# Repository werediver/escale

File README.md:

# Kitchen / coffee scale

This is a kitchen / coffee scale project repository. Contains both the hardware design files and the firmware source code.

## Prototype one

- [Raspberry Pi Pico](https://www.raspberrypi.com/products/raspberry-pi-pico/)
- Firmware in Rust ([escale_fw_rs](escale_fw_rs/))
- Battery powered (AA×2)

## Prototype zero

The firmware source code is at a very early stage of development. See [escale_fw](escale_fw).

The hardware prototype is assembled on a breadboard and consists of the following components:

- [Seeeduino XIAO](https://wiki.seeedstudio.com/Seeeduino-XIAO/)
- [0.96" SSD1315 OLED display](https://wiki.seeedstudio.com/Grove-OLED-Display-0.96-SSD1315/)
- [MikroE Load Cell 2 Click](https://www.mikroe.com/load-cell-2-click)
- Two 12 mm THT-mount push-buttons

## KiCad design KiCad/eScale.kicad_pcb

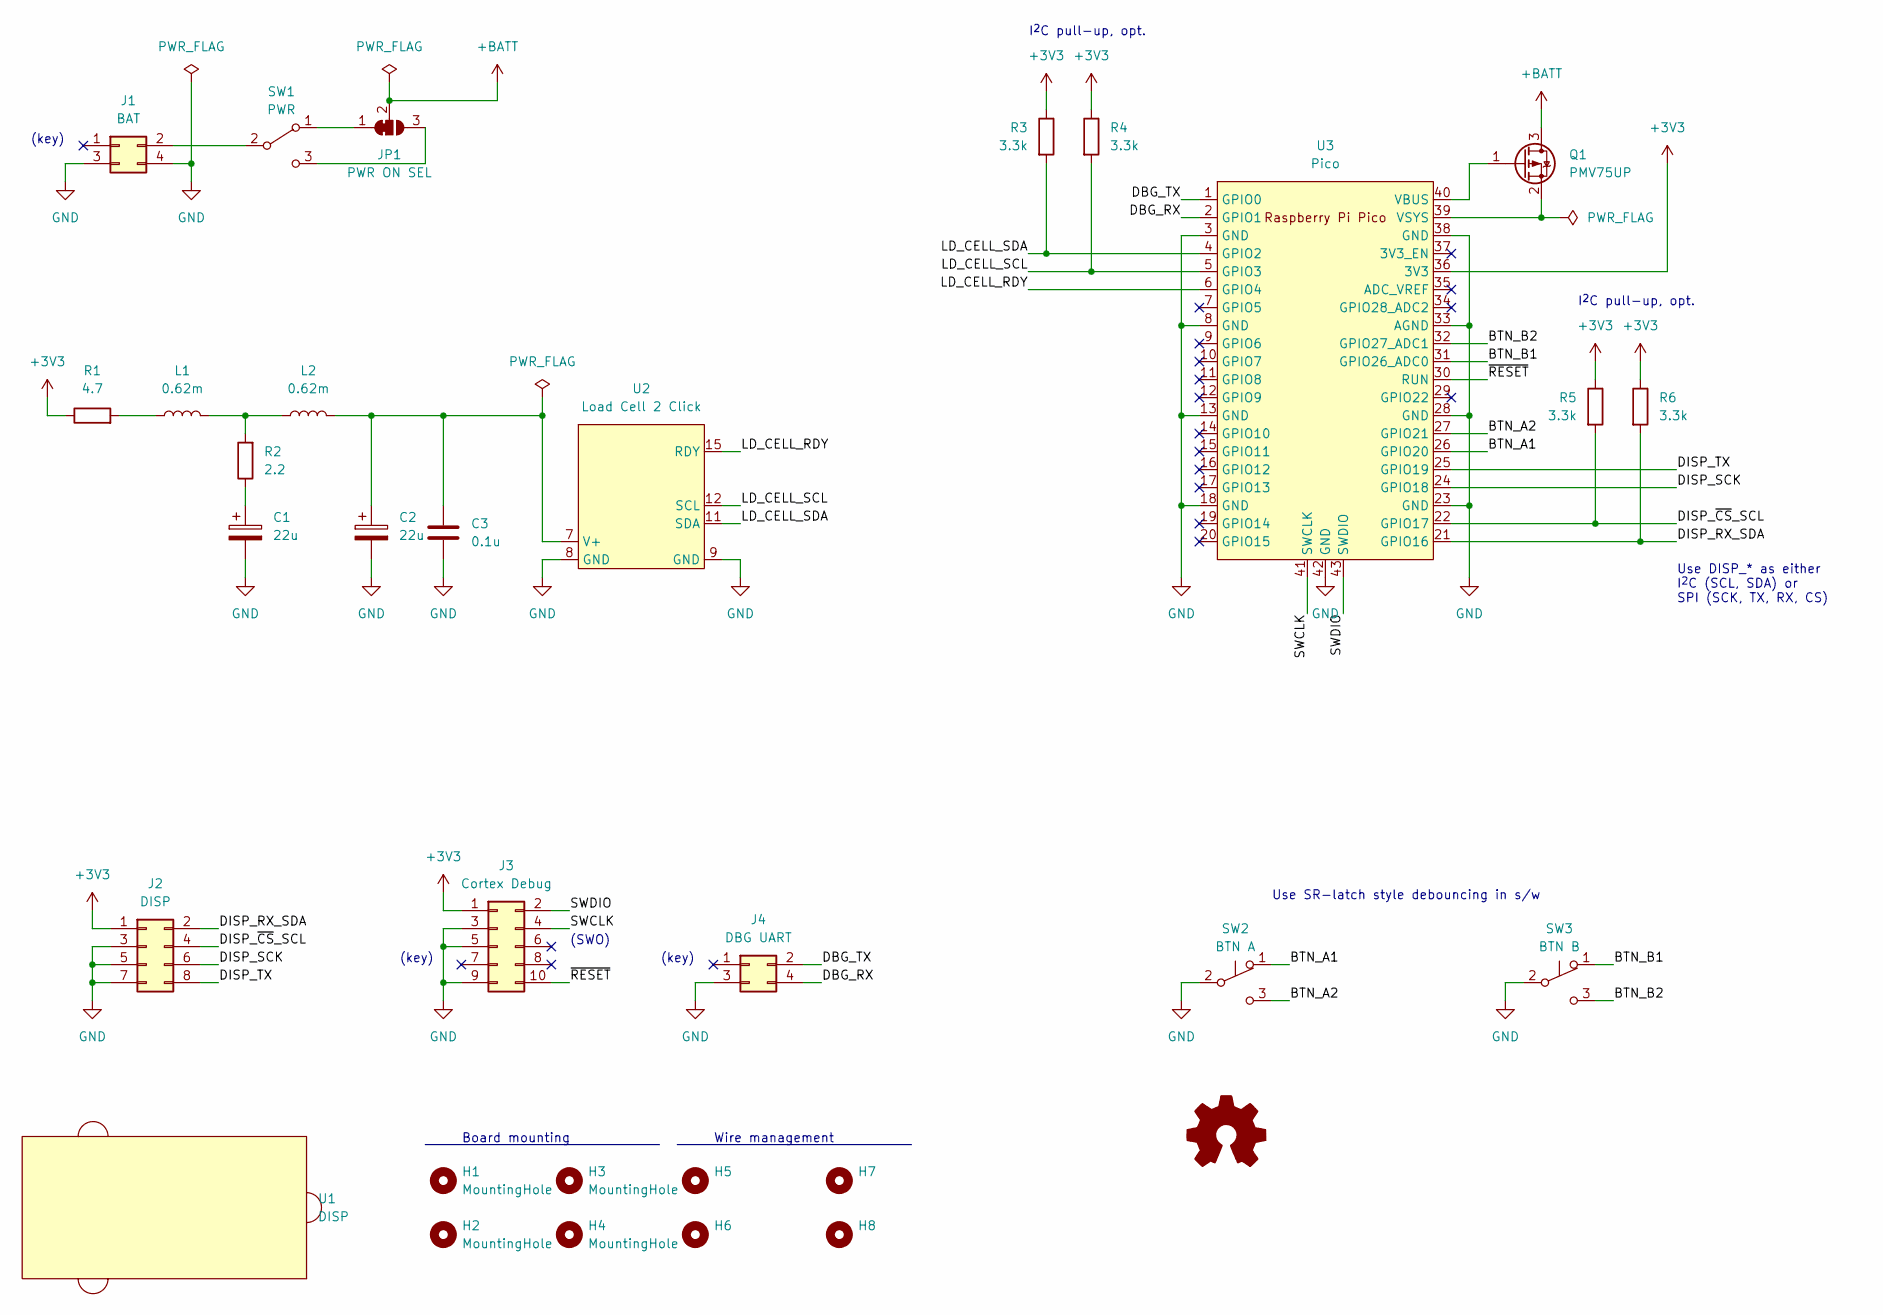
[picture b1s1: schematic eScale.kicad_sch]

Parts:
C1, C2: 22u; CP_Radial_D6.3mm_P2.50mm
C3: 0.1u; C_1206_3216Metric_Pad1.33x1.80mm_HandSolder
H1, H2, H3, H4: MountingHole; MountingHole_3.2mm_M3_Pad
H5, H6, H7, H8: (no value)
J1: BAT; Molex_Milli-Grid_87833-04xx
J2: DISP; Molex_Milli-Grid_87833-08xx
J3: Cortex Debug; Molex_Milli-Grid_87833-10xx
J4: DBG UART; Molex_Milli-Grid_87833-04xx
JP1: PWR ON SEL; SolderJumper-3_P1.3mm_Bridged12_Pad1.0x1.5mm
L1, L2: 0.62m; L_D13.3_d7.3_Horizontal
LOGO1: (no value)
Q1: PMV75UP; SOT-23_Handsoldering
R1: 4.7; R_1206_3216Metric_Pad1.30x1.75mm_HandSolder
R2: 2.2; R_1206_3216Metric_Pad1.30x1.75mm_HandSolder
R3, R4, R5, R6: 3.3k; R_1206_3216Metric_Pad1.30x1.75mm_HandSolder
SW1: PWR; 300SPxxxxxxVS2xx
SW2: BTN A; 300SPxxxxxxVS2xx
SW3: BTN B; 300SPxxxxxxVS2xx
U1: DISP; Seeed_Grove_20x40
U2: Load Cell 2 Click; MikroE Click
U3: Pico; RPi_Pico_SMD_TH

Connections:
+3V3: J2.1, J3.1, R1.1, R3.1, R4.1, R5.1, R6.1, U3.36 (3V3)
+BATT: JP1.2 (C), Q1.3 (D)
/BTN_A1: SW2.1 (A), U3.26 (GPIO20)
/BTN_A2: SW2.3 (C), U3.27 (GPIO21)
/BTN_B1: SW3.1 (A), U3.31 (GPIO26_ADC0)
/BTN_B2: SW3.3 (C), U3.32 (GPIO27_ADC1)
/DBG_RX: J4.4, U3.2 (GPIO1)
/DBG_TX: J4.2, U3.1 (GPIO0)
/DISP_RX_SDA: J2.2, R6.2, U3.21 (GPIO16)
/DISP_SCK: J2.6, U3.24 (GPIO18)
/DISP_TX: J2.8, U3.25 (GPIO19)
/DISP_~CS_SCL: J2.4, R5.2, U3.22 (GPIO17)
/LD_CELL_RDY: U2.15 (RDY), U3.6 (GPIO4)
/LD_CELL_SCL: R4.2, U2.12 (SCL), U3.5 (GPIO3)
/LD_CELL_SDA: R3.2, U2.11 (SDA), U3.4 (GPIO2)
/SWCLK: J3.4, U3.41 (SWCLK)
/SWDIO: J3.2, U3.43 (SWDIO)
/~RESET: J3.10, U3.30 (RUN)
GND: C1.2, C2.2, C3.2, J1.3, J1.4, J2.3, J2.5, J2.7, J3.3, J3.5, J3.9, J4.3, SW2.2 (B), SW3.2 (B), U2.8 (GND), U2.9 (GND), U3.3 (GND), U3.8 (GND), U3.13 (GND), U3.18 (GND), U3.23 (GND), U3.28 (GND), U3.33 (AGND), U3.38 (GND), U3.42 (GND)
unnamed: C1.1, R2.1
unnamed: C2.1, C3.1, L2.2, U2.7 (V+)
unnamed: J1.2, SW1.2 (B)
unnamed: JP1.1 (A), SW1.1 (A)
unnamed: JP1.3 (B), SW1.3 (C)
unnamed: L1.1, R1.2
unnamed: L1.2, L2.1, R2.2
unnamed: Q1.1 (G), U3.40 (VBUS)
unnamed: Q1.2 (S), U3.39 (VSYS)

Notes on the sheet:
(key)
Board mounting
Use SR-latch style debouncing in s/w
I^{2}C pull-up, opt.
Use DISP_* as either I^{2}C (SCL, SDA) or SPI (SCK, TX, RX, CS)
(SWO)
Wire management

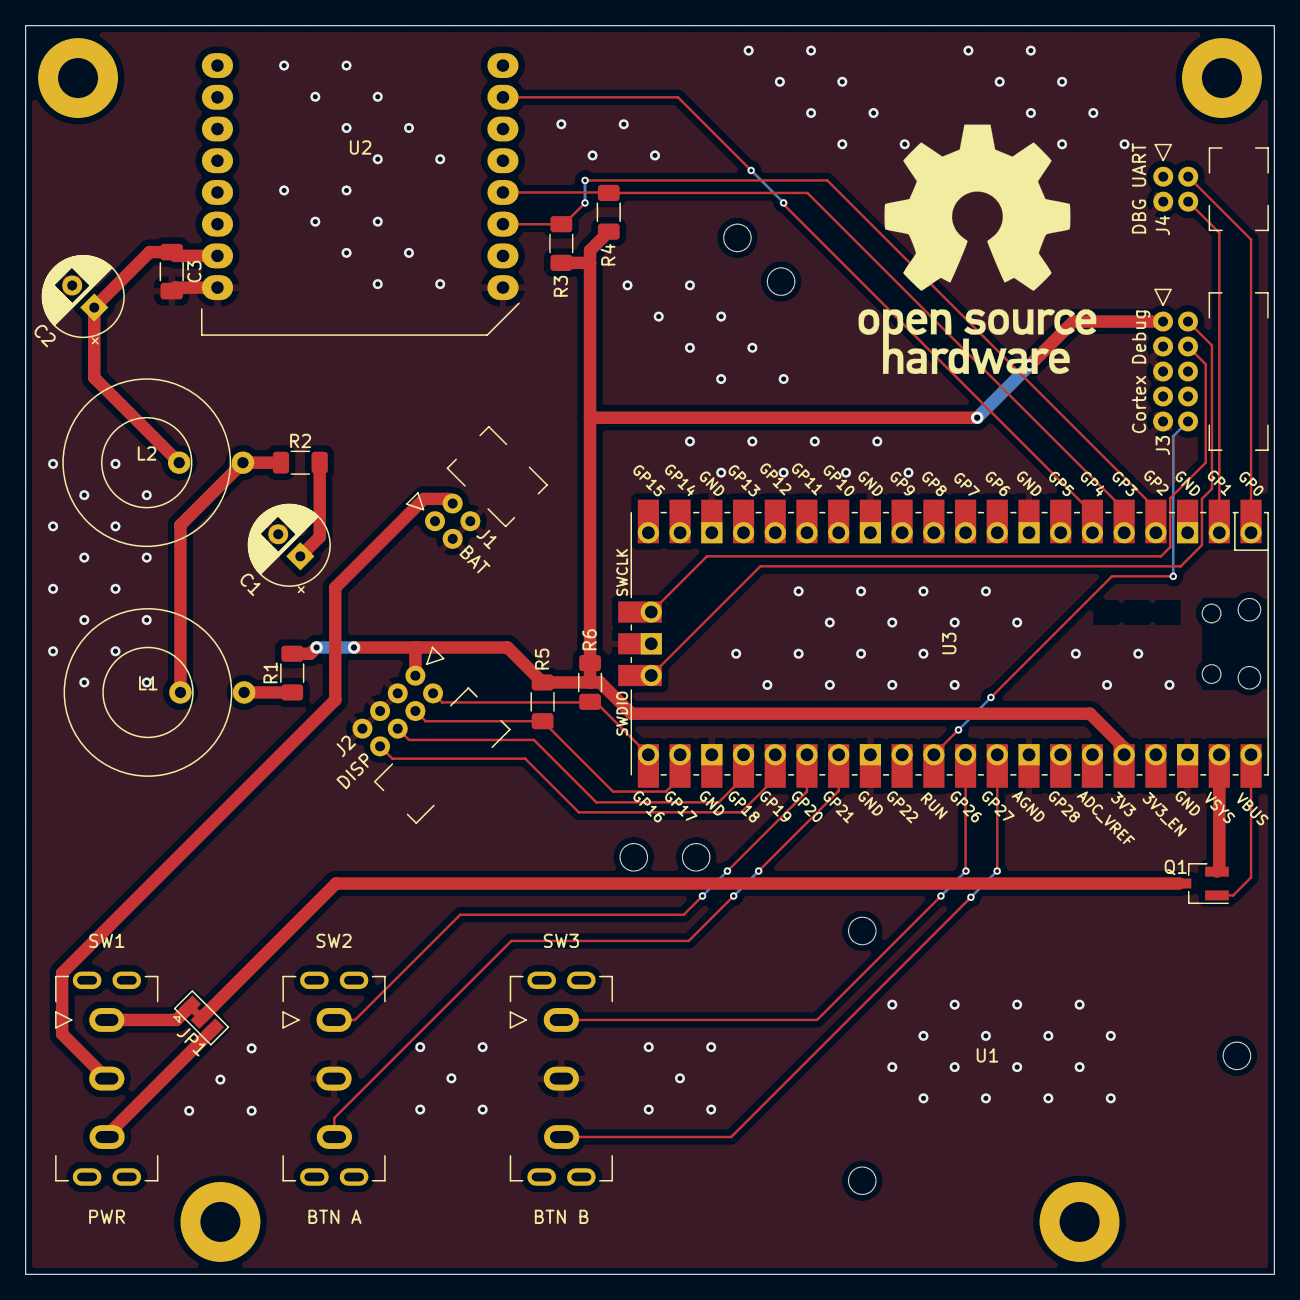
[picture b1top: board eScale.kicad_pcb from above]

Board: 2 copper layers, 100.0 x 100.0 mm, 32 parts (0 on the bottom side), 28 nets.

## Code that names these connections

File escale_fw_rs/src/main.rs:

#![no_std]
#![no_main]
#![feature(alloc_error_handler)]
#![feature(trait_alias)]

mod common;
mod dashboard;
mod input_scanner;
mod run_loop;
mod uptime;
mod uptime_delay;

extern crate alloc;

use alloc::rc::Rc;
use alloc_cortex_m::CortexMHeap;
use core::{alloc::Layout, cell::RefCell};
use cortex_m_rt::entry;
use dashboard::Dashboard;
use embedded_hal::digital::v2::InputPin;
use embedded_time::rate::Extensions;
use panic_probe as _;
use uptime::Uptime;

use rp_pico as bsp;

use bsp::hal::{
    clocks::init_clocks_and_plls,
    gpio::{Pin, PullUpInput},
    pac,
    sio::Sio,
    Clock, Watchdog, I2C,
};

use nau7802::{Gain, Ldo, Nau7802, SamplesPerSecond};
use ssd1306::{
    mode::{TerminalDisplaySize, TerminalMode},
    prelude::{WriteOnlyDataCommand, *},
    I2CDisplayInterface, Ssd1306,
};

use crate::{input_scanner::*, run_loop::*};

#[alloc_error_handler]
fn oom(_: Layout) -> ! {
    loop {}
}

#[global_allocator]
static ALLOCATOR: CortexMHeap = CortexMHeap::empty();

fn init_heap() {
    use core::mem::MaybeUninit;
    const HEAP_SIZE: usize = 128 * 1024;
    static mut HEAP: [MaybeUninit<u8>; HEAP_SIZE] = [MaybeUninit::uninit(); HEAP_SIZE];
    unsafe { ALLOCATOR.init(HEAP.as_ptr() as usize, HEAP_SIZE) }
}

#[entry]
fn _main() -> ! {
    init_heap();

    let mut pac = pac::Peripherals::take().unwrap();
    let sio = Sio::new(pac.SIO);

    let core = pac::CorePeripherals::take().unwrap();
    let mut uptime = Uptime::new(core.SYST);

    let pins = bsp::Pins::new(
        pac.IO_BANK0,
        pac.PADS_BANK0,
        sio.gpio_bank0,
        &mut pac.RESETS,
    );

    let mut watchdog = Watchdog::new(pac.WATCHDOG);

    // External high-speed crystal on the pico board is 12Mhz
    let external_xtal_freq_hz = 12_000_000u32;
    let clocks = init_clocks_and_plls(
        external_xtal_freq_hz,
        pac.XOSC,
        pac.CLOCKS,
        pac.PLL_SYS,
        pac.PLL_USB,
        &mut pac.RESETS,
        &mut watchdog,
    )
    .ok()
    .unwrap();

    let i2c = I2C::i2c0(
        pac.I2C0,
        pins.gpio16.into_mode(),
        pins.gpio17.into_mode(),
        400.kHz(),
        &mut pac.RESETS,
        clocks.system_clock.freq(),
    );

    let interface = I2CDisplayInterface::new(i2c);
    let shared_terminal = Rc::new(RefCell::new(
        Ssd1306::new(interface, DisplaySize128x64, DisplayRotation::Rotate0).into_terminal_mode(),
    ));
    {
        let mut terminal = shared_terminal.borrow_mut();
        terminal.init().unwrap();
        terminal.clear().unwrap();
    }

    let i2c1 = I2C::i2c1(
        pac.I2C1,
        pins.gpio2.into_mode(),
        pins.gpio3.into_mode(),
        400.kHz(),
        &mut pac.RESETS,
        clocks.system_clock.freq(),
    );
    let mut nau7802 = Nau7802::new_with_settings(
        i2c1,
        Ldo::L3v0,
        Gain::G128,
        SamplesPerSecond::SPS10,
        &mut uptime,
    )
    .unwrap();

    let mut cx = AppContext::default();
    let mut schedule: Schedule<AppTask, AppContext> = Schedule::default();

    let button_a_pin: Pin<_, PullUpInput> = pins.gpio20.into_mode();
    let button_b_pin: Pin<_, PullUpInput> = pins.gpio26.into_mode();

    schedule.push(AppTask::InputScanner(InputScanner::new(
        move || button_a_pin.is_low().ok().unwrap(),
        move || button_b_pin.is_low().ok().unwrap(),
    )));

    let dashboard = Dashboard::new(shared_terminal.clone(), Uptime::get_instant);
    schedule.push(AppTask::Dashboard(dashboard));

    loop {
        schedule.run(&mut cx);
        if nau7802.data_available().unwrap() {
            cx.state.weight = (nau7802.read_unchecked().unwrap()) as f32;
        }
    }
}

#[derive(Default)]
struct AppContext {
    mq: MessageQueue<InputEvent>,
    state: AppState,
}

#[derive(Default)]
struct AppState {
    weight: f32,
}

enum AppTask {
    InputScanner(InputScanner),
    Dashboard(Dashboard),
}

impl<'a> AsMut<dyn Task<AppContext> + 'a> for AppTask {
    fn as_mut(&mut self) -> &mut (dyn Task<AppContext> + 'a) {
        match self {
            AppTask::InputScanner(input_scanner) => input_scanner,
            AppTask::Dashboard(dashboard) => dashboard,
        }
    }
}

pub trait Terminal: core::fmt::Write {
    fn clear(&mut self) -> core::fmt::Result;
    fn set_position(&mut self, column: u8, row: u8) -> core::fmt::Result;
}

impl<DI, SIZE> Terminal for Ssd1306<DI, SIZE, TerminalMode>
where
    DI: WriteOnlyDataCommand,
    SIZE: TerminalDisplaySize,
{
    fn clear(&mut self) -> core::fmt::Result {
        self.clear().map_err(|_| core::fmt::Error)
    }

    fn set_position(&mut self, column: u8, row: u8) -> core::fmt::Result {
        self.set_position(column, row).map_err(|_| core::fmt::Error)
    }
}

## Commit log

2021-06-12 Implement interrupt-driven button interface with debouncing
2021-06-17 Implement basic communication with NAU7802
2021-06-22 Introduce a notion of a task, move parts in separate files
2021-06-27 Upgrade fmtlib to v8.0.0
2021-06-27 Reorganize the app structure
2021-06-27 Add top-level README.md
2021-07-01 Introduce `View<State>`
2021-07-03 Rework `AppHAL::InputHandler`, introduce `AppInput::ButtonEvent`
2021-07-03 Rename `overloaded` to `overload`
2021-07-04 Embed input handling into `UI::View` (draft)
    Also
    - introduce `UI::`, move `View`, `SomeView`, `AppInput::InputHandler` to `UI::`
    - introduce `Unit` (an empty final struct)
2021-07-05 Rework `UI::SomeView` to allow implementing views through subclassing
2021-07-08 Introduce `RunLoop` and convert view stack rendering routine into ``
    Note: `RunLoop.find` requires RTTI.
2021-07-12 Set up `clang-tidy` as the static analysis tool
2021-07-12 Introduce `DashboardTask`, rework header guards, use `= default` destructors in interfaces, clean up
2021-07-13 Use `enum class`, use member initializers
    Thanks, Kate Gregory! https://youtu.be/XkDEzfpdcSg
2021-07-17 Fix `readButtons` (reading from an empty vector), introduce "debug" module
2021-07-17 Make `DashboardTask` access its state via a getter (no duck-typing), rename `SomeView` to `BaseView`
2021-07-20 Add taring view
2021-07-24 Introduce `BaseTask`
2021-07-24 Clean up the app state
2021-07-24 Update weight averaging four samples
2021-08-07 Some Octave code to design FIR filters
2022-02-05 Latest (WIP) changes with taring, calibration, and some filtering
2022-05-01 Add the KiCad files for a Raspberry Pi Pico based board
2022-07-17 A "run-loop" sketch in Rust
2022-07-17 A template "blinky" in Rust
2022-07-17 Introduce `Button` helper (in "input_scanner.rs)
2022-07-21 Implement a stopwatch (based on SysTick timer)
2022-07-23 Basic interfacing with NAU7802
2022-08-01 Restructure the project to allow running unit-tests on the host system
2022-08-01 Introduce `Ring.is_filled()` and `Ring.reset()`
2022-08-01 Introduce `Scale`
    Extract the message queue into a separate file
    Rewrite `mean()` to accept an iterator
2022-08-03 Introduce "app-core" crate
2022-09-27 Introduce `RingState`, index management for a ring buffer
2022-09-27 Minor improvements to "flash.rs"
2022-09-27 Introduce `Ring.retain()`, `.retain_mut()`, `.append()`
2022-09-27 Replace the use of "flash_static.rs" with a new implementation (not relying on static vars anymore)
2022-09-27 Make `MessageQueue` use `Ring` as the underlying collection
2022-09-27 Automatically tare on start-up
2022-09-27 Support long press
2022-09-27 Clean-up & changes after Clippy warnings
2022-09-27 Introduce `FnTask`
2022-09-27 Move "dashboard.rs" to "app-core"
2022-09-27 Rename "flash.rs" to "flash_static.rs"
2022-09-27 Persist the calibration parameter
2022-09-27 Rename `Ring` to `SimpleRing`
2022-09-27 Introduce "ring" crate
2024-02-25 Update dependencies
